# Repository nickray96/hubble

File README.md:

# hubble
A switched USB hub. 

# Rev 1.0:
* USB 2.0 and USB 3.0
* Tested working (see errata)
* Toggle SW1 to select between host 1 and 2
* Debug connector provides I2C to use via TotalPhase Aardvark (or other debug device)
  * Also routed to USB-C SBU

## Errata
* USB5744 does not enter runtime, looks for I2C host. Remove R14 and R17, puts hub in headless mode.

# Rev 2.0:
* Enable USB5744 port power toggling
* Optionally drive mux sel via Raspberry Pi Pico W (useful for home automation)
* Add DisplayPort mux so I can stop using my monitor OSD (TBD which connectors I'll use)

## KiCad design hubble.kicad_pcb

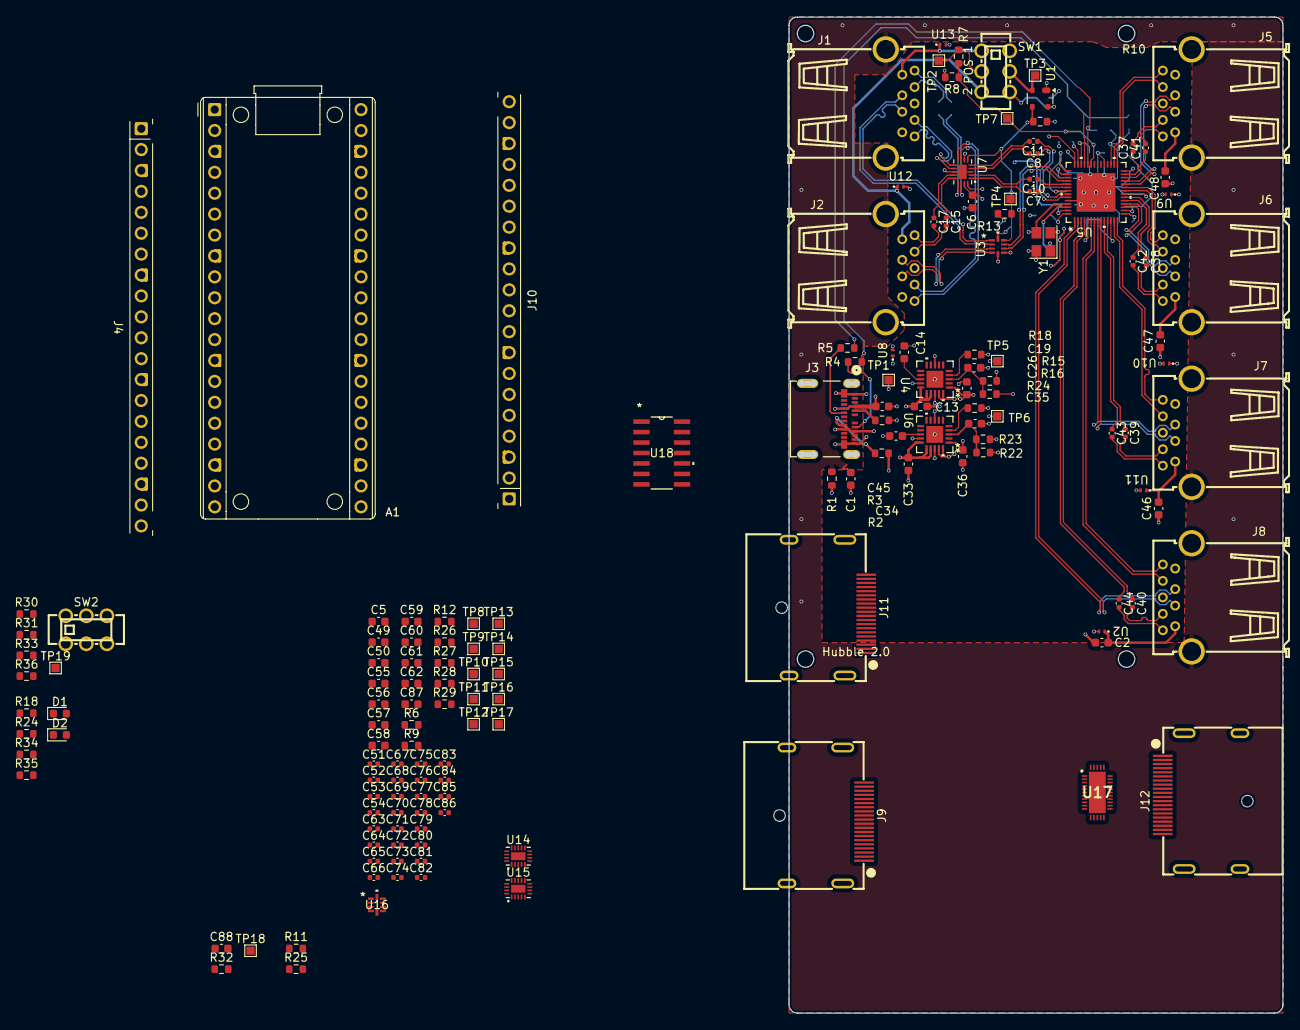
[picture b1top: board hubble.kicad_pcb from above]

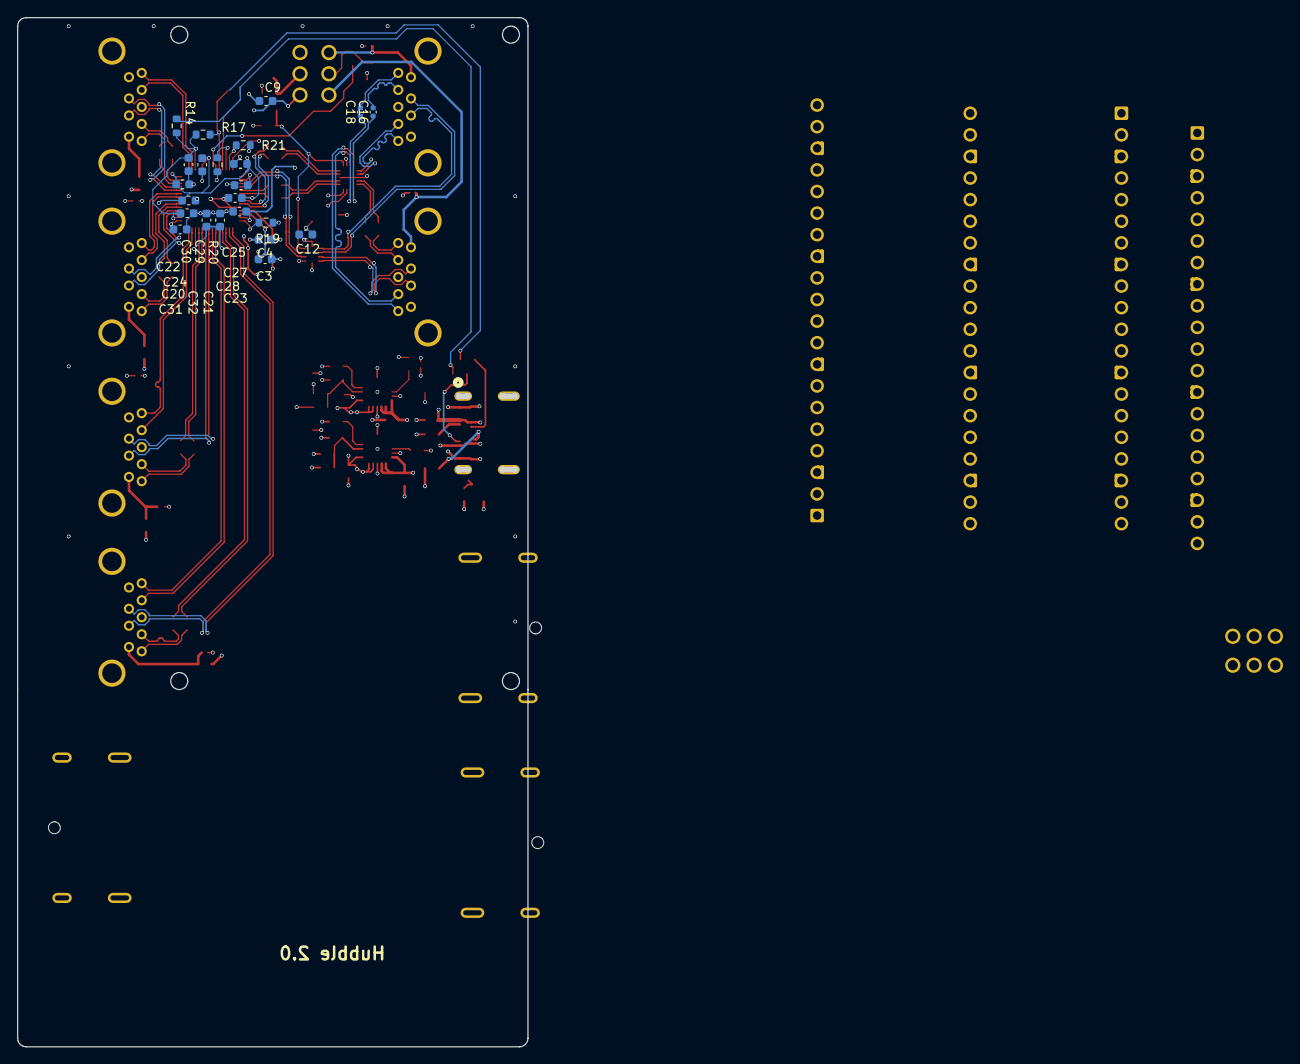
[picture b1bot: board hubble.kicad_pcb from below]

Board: 4 copper layers, 61.9 x 121.0 mm, 181 parts (23 on the bottom side), 181 nets.

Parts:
A1: RaspberryPi_Pico_W; RaspberryPi_Pico_Common_THT
C1, C5, C6, C9, C12, C14, C19, C20, C21, C22, C23, C24, C25, C27, C28, C29, C30, C31, C32, C34, C35, C49, C50, C55, C56, C57, C58, C59, C60, C61, C87, C88: 0.1uF; C_0603_1608Metric
C2, C45, C46, C47, C48: 2.2uF; C_0603_1608Metric
C3, C4: 20pF; C_0603_1608Metric
C7, C8, C10, C11, C15, C16, C17, C18, C37, C38, C39, C40, C41, C42, C43, C44, C51, C52, C53, C54, C63, C64, C65, C66, C67, C68, C69, C70, C71, C72, C73, C74, C75, C76, C77, C78, C79, C80, C81, C82, C83, C84, C85, C86: 0.1uF; C_0402_1005Metric
C13, C33: 10uF; C_0603_1608Metric
C26, C36: 22uF; C_0603_1608Metric
C62: 4.7uF; C_0603_1608Metric
D1, D2: LED_green; LED_0603_1608Metric
J1, J2, J5, J6, J7, J8: USB3_A_LCSC; USB-TH_XUNPU_USB-301WD-ARY
J3: USB_C_Receptacle_Molex; USB_C_CONN_105450-0101_MOLEX
J4: Pico_Socket_A; RaspberryPi_Pico_PinSocket_1x20_P2.54mm_Vertical
J9, J11, J12: DisplayPort; DISPLAYPORT_XDPF-0205-20S
J10: Pico_Socket_B; RaspberryPi_Pico_PinSocket_1x20_P2.54mm_Vertical
R1, R6, R9, R24#2, R29, R35: 330; R_0603_1608Metric
R2, R3: 5.1k; R_0603_1608Metric
R4, R5, R11, R25: 0; R_0603_1608Metric
R7, R18, R24: 50k; R_0603_1608Metric
R8: 100k; R_0603_1608Metric
R10, R13, R14, R17, R18#2, R26, R27, R30, R32, R34, R36: 10k; R_0603_1608Metric
R12, R28: 1M; R_0603_1608Metric
R15: 11.8k; R_0603_1608Metric
R16: 3.74k; R_0603_1608Metric
R19: 12k; R_0603_1608Metric
R20, R21: 200k; R_0603_1608Metric
R22: 12.4k; R_0603_1608Metric
R23: 24.9k; R_0603_1608Metric
R31, R33: 27; R_0603_1608Metric
SW1, SW2: K3-2235D-F1; SW-TH_K3-2235D-F1
TP1, TP2, TP3, TP4, TP5, TP6, TP7, TP8, TP9, TP10, TP11, TP12, TP13, TP14, TP15, TP16, TP17, TP18, TP19: TestPoint; TestPoint_Pad_1.0x1.0mm
U1: MAX6816EUS+T; SOT-143
U2, U8, U9, U10, U11, U12, U13: TPD1E05U06DPY; Texas_DPY0002A_0.6x1mm_P0.65mm
U3, U16: TS3USB221RSER; UQFN-10
U4, U6: TPS7A5201QRGRRQ1; RGR20_2P05X2P05_TEX
U5: USB5744; VQFN56_2G_MCH
U7, U14, U15: FUSB340; TMLP-18_L2.8-W2.0-P0.40-BL-EP
U17: PI3DPX1203BZLEX; QFN40P300X600X80-33N
U18: SN74CBTLV3126DR; D14
Y1: X322525MOB4SI; Crystal_SMD_3225-4Pin_3.2x2.5mm

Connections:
/DisplayPort/DP_HOST0_AUX_N: C54.2, U16.2 (1D-)
/DisplayPort/DP_HOST0_AUX_P: C51.2, U16.1 (1D+)
/DisplayPort/DP_HOST0_D0_N: C64.1, J9.3 (D0_N)
/DisplayPort/DP_HOST0_D0_P: C63.1, J9.1 (D0_P)
/DisplayPort/DP_HOST0_D1_N: C66.1, J9.6 (D1_N)
/DisplayPort/DP_HOST0_D1_P: C65.1, J9.4 (D1_P)
/DisplayPort/DP_HOST0_D2_N: C68.1, J9.9 (D2_N)
/DisplayPort/DP_HOST0_D2_P: C67.1, J9.7 (D2_P)
/DisplayPort/DP_HOST0_D3_N: C70.1, J9.12 (D3_N)
/DisplayPort/DP_HOST0_D3_P: C69.1, J9.10 (D3_P)
/DisplayPort/DP_HOST0_HPD: J9.18 (HPD), U18.2 (1A)
/DisplayPort/DP_HOST1_AUX_N: C53.2, U16.4 (2D-)
/DisplayPort/DP_HOST1_AUX_P: C52.2, U16.3 (2D+)
/DisplayPort/DP_HOST1_D0_N: C81.1, J11.3 (D0_N)
/DisplayPort/DP_HOST1_D0_P: C79.1, J11.1 (D0_P)
/DisplayPort/DP_HOST1_D1_N: C85.1, J11.6 (D1_N)
/DisplayPort/DP_HOST1_D1_P: C83.1, J11.4 (D1_P)
/DisplayPort/DP_HOST1_D2_N: C82.1, J11.9 (D2_N)
/DisplayPort/DP_HOST1_D2_P: C80.1, J11.7 (D2_P)
/DisplayPort/DP_HOST1_D3_N: C86.1, J11.12 (D3_N)
/DisplayPort/DP_HOST1_D3_P: C84.1, J11.10 (D3_P)
/DisplayPort/DP_HOST1_HPD: J11.18 (HPD), U18.5 (2A)
/DisplayPort/DP_SINK_AUX_N: J12.17 (AUX_N), U16.7 (D-)
/DisplayPort/DP_SINK_AUX_P: J12.15 (AUX_P), U16.8 (D+)
/DisplayPort/DP_SINK_HPD: J12.18 (HPD), U18.3 (1B), U18.6 (2B)
/DisplayPort/I2C_SCL: J4.5 (GPIO3), R5.2, R11.1, R14.2, U17.13 (SCL)
/DisplayPort/I2C_SDA: J4.4 (GPIO2), R4.2, R17.2, R25.1, U17.12 (SDA)
/DisplayPort/MUX_SEL: R10.1, R13.1, TP4.1, U1.3 (OUT), U3.9 (S), U7.6 (S), U14.6 (S), U15.6 (S), U16.9 (S), U18.4 (2OE)
/DisplayPort/~DP_RST: R27.1, U17.29 (FG1/I2C_RESET#)
/DisplayPort/~MUX_SEL: R32.1, TP18.1, U18.1 (1OE)
/Hub/DEVICE_1_USB_N: J8.2 (D-), U5.2 (USB2DN_DM1/PRT_DIS_M1)
/Hub/DEVICE_1_USB_P: J8.3 (D+), U5.1 (USB2DN_DP1/PRT_DIS_P1)
/Hub/DEVICE_2_USB_N: J7.2 (D-), U5.9 (USB2DN_DM2/PRT_DIS_M2)
/Hub/DEVICE_2_USB_P: J7.3 (D+), U5.8 (USB2DN_DP2/PRT_DIS_P2)
/Hub/DEVICE_3_USB_N: J6.2 (D-), U5.18 (USB2DN_DM3/PRT_DIS_M3)
/Hub/DEVICE_3_USB_P: J6.3 (D+), U5.17 (USB2DN_DP3/PRT_DIS_P3)
/Hub/DEVICE_4_USB_N: J5.2 (D-), U5.25 (USB2DN_DM4/PRT_DIS_M4)
/Hub/DEVICE_4_USB_P: J5.3 (D+), U5.24 (USB2DN_DP4/PRT_DIS_P4)
/Hub/HOST_1_USB_N: J1.2 (D-), U3.2 (1D-)
/Hub/HOST_1_USB_P: J1.3 (D+), U3.1 (1D+)
/Hub/HOST_2_USB_N: J2.2 (D-), U3.4 (2D-)
/Hub/HOST_2_USB_P: J2.3 (D+), U3.3 (2D+)
/Hub/HUB_USB_N: U3.7 (D-), U5.46 (USB2UP_DM)
/Hub/HUB_USB_P: U3.8 (D+), U5.45 (USB2UP_DP)
/Hub/SS_RX_DEVICE_1_N: J8.5 (SSRX-), U5.7 (USB3DN_RXDM1)
/Hub/SS_RX_DEVICE_1_P: J8.6 (SSRX+), U5.6 (USB3DN_RXDP1)
/Hub/SS_RX_DEVICE_2_N: J7.5 (SSRX-), U5.14 (USB3DN_RXDM2)
/Hub/SS_RX_DEVICE_2_P: J7.6 (SSRX+), U5.13 (USB3DN_RXDP2)
/Hub/SS_RX_DEVICE_3_N: J6.5 (SSRX-), U5.23 (USB3DN_RXDM3)
/Hub/SS_RX_DEVICE_3_P: J6.6 (SSRX+), U5.22 (USB3DN_RXDP3)
/Hub/SS_RX_DEVICE_4_N: J5.5 (SSRX-), U5.30 (USB3DN_RXDM4)
/Hub/SS_RX_DEVICE_4_P: J5.6 (SSRX+), U5.29 (USB3DN_RXDP4)
/Hub/SS_RX_HOST_1_N: J1.5 (SSRX-), U7.10 (SSRX1+)
/Hub/SS_RX_HOST_1_P: J1.6 (SSRX+), U7.11 (SSRX1-)
/Hub/SS_RX_HOST_2_N: J2.5 (SSRX-), U7.9 (SSRX2-)
/Hub/SS_RX_HOST_2_P: J2.6 (SSRX+), U7.8 (SSRX2+)
/Hub/SS_RX_HUB_CAP_N: C8.1, U7.4 (SSRXCOM-)
/Hub/SS_RX_HUB_CAP_P: C7.1, U7.5 (SSRXCOM+)
/Hub/SS_RX_HUB_N: C8.2, U5.51 (USB3UP_RXDM)
/Hub/SS_RX_HUB_P: C7.2, U5.50 (USB3UP_RXDP)
/Hub/SS_TX_DEVICE_1_CAP_N: C40.1, U5.4 (USB3DN_TXDM1)
/Hub/SS_TX_DEVICE_1_CAP_P: C44.1, U5.3 (USB3DN_TXDP1)
/Hub/SS_TX_DEVICE_1_N: C40.2, J8.8 (SSTX-)
/Hub/SS_TX_DEVICE_1_P: C44.2, J8.9 (SSTX+)
/Hub/SS_TX_DEVICE_2_CAP_N: C39.1, U5.11 (USB3DN_TXDM2)
/Hub/SS_TX_DEVICE_2_CAP_P: C43.1, U5.10 (USB3DN_TXDP2)
/Hub/SS_TX_DEVICE_2_N: C39.2, J7.8 (SSTX-)
/Hub/SS_TX_DEVICE_2_P: C43.2, J7.9 (SSTX+)
/Hub/SS_TX_DEVICE_3_CAP_N: C38.1, U5.20 (USB3DN_TXDM3)
/Hub/SS_TX_DEVICE_3_CAP_P: C42.1, U5.19 (USB3DN_TXDP3)
/Hub/SS_TX_DEVICE_3_N: C38.2, J6.8 (SSTX-)
/Hub/SS_TX_DEVICE_3_P: C42.2, J6.9 (SSTX+)
/Hub/SS_TX_DEVICE_4_CAP_N: C37.1, U5.27 (USB3DN_TXDM4)
/Hub/SS_TX_DEVICE_4_CAP_P: C41.1, U5.26 (USB3DN_TXDP4)
/Hub/SS_TX_DEVICE_4_N: C37.2, J5.8 (SSTX-)
/Hub/SS_TX_DEVICE_4_P: C41.2, J5.9 (SSTX+)
/Hub/SS_TX_HOST_1_CAP_N: C16.2, U7.15 (SSTX1+)
/Hub/SS_TX_HOST_1_CAP_P: C15.2, U7.16 (SSTX1-)
/Hub/SS_TX_HOST_1_N: C16.1, J1.8 (SSTX-)
/Hub/SS_TX_HOST_1_P: C15.1, J1.9 (SSTX+)
/Hub/SS_TX_HOST_2_CAP_N: C17.2, U7.14 (SSTX2-)
/Hub/SS_TX_HOST_2_CAP_P: C18.2, U7.13 (SSTX2+)
/Hub/SS_TX_HOST_2_N: C17.1, J2.8 (SSTX-)
/Hub/SS_TX_HOST_2_P: C18.1, J2.9 (SSTX+)
/Hub/SS_TX_HUB_CAP_N: C11.1, U7.1 (SSTXCOM-)
/Hub/SS_TX_HUB_CAP_P: C10.1, U7.2 (SSTXCOM+)
/Hub/SS_TX_HUB_N: C11.2, U5.48 (USB3UP_TXDM)
/Hub/SS_TX_HUB_P: C10.2, U5.47 (USB3UP_TXDP)
/Hub/VBUS_DET: R7.2, R8.1, TP7.1, U5.37 (VBUS_DET)
/Hub/VBUS_DET_1: J1.1 (VBUS), SW1.4 (A), U13.1 (I/O)
/Hub/VBUS_DET_2: J2.1 (VBUS), SW1.6 (C), U12.1 (I/O)
/MCU/MUX_SEL_MANUAL: SW1.2 (B), SW2.1 (A)
/MCU/MUX_SEL_MCU: J4.1 (GPIO0), R30.1, SW2.3 (C)
/MCU/PI_RUN: J10.10 (RUN), SW2.5 (B)
/Power/MCU_USB_DN: J3.A7 (D-), J3.B7 (D-)
/Power/MCU_USB_DP: J3.A6 (D+), J3.B6 (D+)
GND: C1.1, C2.1, C3.1, C4.1, C5.1, C6.1, C9.1, C12.1, C13.1, C14.1, C20.2, C21.2, C22.2, C23.2, C24.2, C25.2, C26.1, C27.2, C28.2, C29.2, C30.2, C31.2, C32.2, C33.1, C34.1, C36.1, C45.1, C46.1, C47.1, C48.1, C49.1, C50.1, C55.1, C56.1, C57.1, C58.2, C59.2, C60.2, C61.2, C62.2, C87.1, C88.1, J1.4 (GND), J1.7 (DRAIN), J2.4 (GND), J2.7 (DRAIN), J3.A1 (GND), J3.A12 (GND), J3.B1 (GND), J3.B12 (GND), J4.3 (GND), J4.8 (GND), J4.13 (GND), J4.18 (GND), J5.4 (GND), J5.7 (DRAIN), J6.4 (GND), J6.7 (DRAIN), J7.4 (GND), J7.7 (DRAIN), J8.4 (GND), J8.7 (DRAIN), J9.2 (GND), J9.5 (GND), J9.8 (GND), J9.11 (GND), J9.16 (GND), J10.3 (GND), J10.8 (GND), J10.13 (AGND), J10.18 (GND), J11.2 (GND), J11.5 (GND), J11.8 (GND), J11.11 (GND), J11.16 (GND), J12.19 (DP_PWR_RET), R1.2, R2.2, R3.2, R6.2, R8.2, R9.2, R10.2, R12.2, R13.2, R16.2, R19.1, R20.2, R21.2, R23.2, R24#2.2, R27.2, R28.2, R29.2, R30.2, R32.2, R35.2, SW1.1 (A), SW2.4 (A), U1.1 (GND), U2.2 (GND), U3.5 (GND), U3.6 (*OE), U4.8 (GND), U4.18 (GND), U4.21 (EPAD), U5.52 (ATEST), U5.57 (PAD), U6.8 (GND), U6.18 (GND), U6.21 (EPAD), U7.3 (GND), U7.7 (OE#), U7.12 (GND), U7.18 (GND), U7.19 (GND), U8.2 (GND), U9.2 (GND), U10.2 (GND), U11.2 (GND), U12.2 (GND), U13.2 (GND), U14.3 (GND), U14.7 (OE#), U14.12 (GND), U14.18 (GND), U14.19 (GND), U15.3 (GND), U15.7 (OE#), U15.12 (GND), U15.18 (GND), U15.19 (GND), U16.5 (GND), U16.6 (*OE), U17.14 (PRSNT#), U17.33 (GND), U18.7 (GND), Y1.2, Y1.4
unnamed: A1.3 (GND), A1.8 (GND), A1.13 (GND), A1.18 (GND), A1.23 (GND), A1.28 (GND), A1.38 (GND)
unnamed: D1.2 (A), R34.2, U6.4 (PG)
unnamed: D1.1 (K), R24#2.1
unnamed: D2.2 (A), R18#2.2, U4.4 (PG)
unnamed: D2.1 (K), R35.1
unnamed: J3.A5 (CC1), R3.1
unnamed: J3.B5 (CC2), R2.1
unnamed: J3.A8 (SBU1), R4.1
unnamed: J3.B8 (SBU2), R5.1
unnamed: C54.1, J9.17 (AUX_N)
unnamed: C51.1, J9.15 (AUX_P)
unnamed: J9.13 (CFG1), TP13.1
unnamed: J9.14 (CFG2), TP14.1
unnamed: C53.1, J11.17 (AUX_N)
unnamed: C52.1, J11.15 (AUX_P)
unnamed: J11.13 (CFG1), TP11.1
unnamed: J11.14 (CFG2), TP12.1
unnamed: J12.13 (CFG1), R28.1
unnamed: J12.14 (CFG2), R12.1
unnamed: C73.2, J12.3 (D0_N)
unnamed: C71.2, J12.1 (D0_P)
unnamed: C77.2, J12.6 (D1_N)
unnamed: C75.2, J12.4 (D1_P)
unnamed: C74.2, J12.9 (D2_N)
unnamed: C72.2, J12.7 (D2_P)
unnamed: C78.2, J12.12 (D3_N)
unnamed: C76.2, J12.10 (D3_P)
unnamed: R7.1, SW1.5 (B), TP2.1
unnamed: R36.2, SW2.6 (C)
unnamed: SW2.2 (B), TP3.1, U1.2 (IN)
unnamed: C19.1, R15.2, R16.1, U4.3 (FB)
unnamed: C14.2, U4.13 (NR/SS)
unnamed: R19.2, U5.56 (RBIAS)
unnamed: R21.1, U5.41 (SPI_CE_N/CFG_NON_REM)
unnamed: R11.2, U5.38 (SPI_CLK/SMCLK)
unnamed: R20.1, U5.40 (SPI_DI/CFG_BC_EN)
unnamed: R25.2, U5.39 (SPI_DO/SMDAT)
unnamed: C3.2, U5.54 (XTALI/CLK_IN), Y1.1
unnamed: C4.2, U5.53 (XTALO), Y1.3
unnamed: C35.1, R22.2, R23.1, U6.3 (FB)
unnamed: C34.2, U6.13 (NR/SS)
unnamed: C65.2, U14.10 (SSRX1+)
unnamed: C66.2, U14.11 (SSRX1-)
unnamed: C83.2, U14.8 (SSRX2+)
unnamed: C85.2, U14.9 (SSRX2-)
unnamed: U14.5 (SSRXCOM+), U17.4 (A1RX+)
unnamed: U14.4 (SSRXCOM-), U17.5 (A1RX-)
unnamed: C63.2, U14.15 (SSTX1+)
unnamed: C64.2, U14.16 (SSTX1-)
unnamed: C79.2, U14.13 (SSTX2+)
unnamed: C81.2, U14.14 (SSTX2-)
unnamed: U14.2 (SSTXCOM+), U17.1 (A0RX+)
unnamed: U14.1 (SSTXCOM-), U17.2 (A0RX-)
unnamed: C69.2, U15.10 (SSRX1+)
unnamed: C70.2, U15.11 (SSRX1-)
unnamed: C84.2, U15.8 (SSRX2+)
unnamed: C86.2, U15.9 (SSRX2-)
unnamed: U15.5 (SSRXCOM+), U17.10 (A3RX+)
unnamed: U15.4 (SSRXCOM-), U17.11 (A3RX-)
unnamed: C67.2, U15.15 (SSTX1+)
unnamed: C68.2, U15.16 (SSTX1-)
unnamed: C80.2, U15.13 (SSTX2+)
unnamed: C82.2, U15.14 (SSTX2-)
unnamed: U15.2 (SSTXCOM+), U17.7 (A2RX+)
unnamed: U15.1 (SSTXCOM-), U17.8 (A2RX-)
unnamed: C73.1, U17.27 (A0TX+)
unnamed: C71.1, U17.26 (A0TX-)
unnamed: C77.1, U17.24 (A1TX+)
unnamed: C75.1, U17.23 (A1TX-)
unnamed: C74.1, U17.21 (A2TX+)
unnamed: C72.1, U17.20 (A2TX-)
unnamed: C78.1, U17.18 (A3TX+)
unnamed: C76.1, U17.17 (A3TX-)
unnamed: R26.2, U17.15 (ENI2C)
unnamed: TP16.1, U18.9 (3A)
unnamed: TP17.1, U18.8 (3B)
unnamed: TP15.1, U18.10 (3OE)
unnamed: TP9.1, U18.12 (4A)
unnamed: TP10.1, U18.11 (4B)
unnamed: TP8.1, U18.13 (4OE)
Shield: C1.2, C5.2, C49.2, C55.2, J1.10 (SHIELD), J2.10 (SHIELD), J5.10 (SHIELD), J6.10 (SHIELD), J7.10 (SHIELD), J8.10 (SHIELD), J12.2 (GND), J12.5 (GND), J12.8 (GND), J12.11 (GND), J12.16 (GND), R1.1, R6.1, R9.1, R29.1
VBUS_IN: C2.2, C13.2, C33.2, C45.2, C46.2, C47.2, C48.2, J3.A4 (VBUS), J3.A9 (VBUS), J3.B4 (VBUS), J3.B9 (VBUS), J5.1 (VBUS), J6.1 (VBUS), J7.1 (VBUS), J8.1 (VBUS), J10.19 (VSYS), J10.20 (VBUS), TP1.1, U2.1 (I/O), U4.14 (EN), U4.15 (IN), U4.16 (IN), U4.17 (IN), U6.14 (EN), U6.15 (IN), U6.16 (IN), U6.17 (IN), U8.1 (I/O), U9.1 (I/O), U10.1 (I/O), U11.1 (I/O)
VCC_1.2V: C21.1, C22.1, C24.1, C25.1, C28.1, C29.1, C31.1, C32.1, C35.2, C36.2, R22.1, R24.1, TP6.1, U5.5 (VDD12), U5.12 (VDD12), U5.15 (VDD12), U5.21 (VDD12), U5.28 (VDD12), U5.33 (VDD12), U5.43 (VDD12), U5.49 (VDD12), U6.1 (OUT), U6.19 (OUT), U6.20 (OUT)
VCC_3.3V: C6.2, C9.2, C12.2, C19.2, C20.1, C23.1, C26.2, C27.1, C30.1, C50.2, C56.2, C57.2, C58.1, C59.1, C60.1, C61.1, C62.1, C87.2, C88.2, J12.20 (DP_PWR), R14.1, R15.1, R17.1, R18.1, R18#2.1, R26.1, R34.1, R36.1, SW1.3 (C), TP5.1, U1.4 (VCC), U3.10 (VCC), U4.1 (OUT), U4.19 (OUT), U4.20 (OUT), U5.16 (VDD33), U5.31 (VDD33), U5.42 (RESET_N), U5.44 (VDD33), U5.55 (VDD33), U7.17 (VDD), U14.17 (VDD), U15.17 (VDD), U16.10 (VCC), U17.3 (VDD), U17.6 (VDD_2), U17.9 (VDD_3), U17.19 (VDD_4), U17.22 (VDD_5), U17.25 (VDD_6), U17.28 (FG0), U17.30 (EQ1/AD1), U17.31 (EQ2/AD2), U17.32 (EQ3/AD3), U18.14 (VCC)

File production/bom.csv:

Designator,Footprint,Quantity,Value,LCSC Part #
"C1, C10, C11, C12, C14, C15, C16, C17, C18, C19, C20, C21, C22, C23, C24, C25, C27, C28, C29, C30, C31, C32, C34, C35, C37, C38, C39, C40, C41, C42, C43, C44, C6, C7, C8, C9",0603,36,0.1uF,
"C13, C33",0603,2,10uF,
"C2, C45, C46, C47, C48",0603,5,2.2uF,
"C26, C36",0603,2,22uF,
"C3, C4",0603,2,20pF,
"J1, J2, J5, J6, J7, J8",USB-TH_XUNPU_USB-301WD-ARY,6,USB3_A_LCSC,C2895025
J3,USB_C_CONN_105450-0101_MOLEX,1,USB_C_Receptacle_Molex,C134092
J9,PinHeader_2x02_P2.54mm_Vertical,1,Conn_02x02_Odd_Even,
R1,0603,1,330,
"R10, R13, R14, R17",0603,4,10k,
R15,0603,1,11.8k,
R16,0603,1,3.74k,
"R18, R24, R7",0603,3,50k,
R19,0603,1,12k,
"R2, R3",0603,2,5.1k,
"R20, R21",0603,2,200k,
R22,0603,1,12.4k,
R23,0603,1,24.9k,
"R4, R5",0603,2,0,
R8,0603,1,100k,
SW1,SW-TH_K3-2235D-F1,1,K3-2235D-F1,C189615
"TP1, TP2, TP3, TP4, TP5, TP6, TP7",TestPoint_Pad_1.0x1.0mm,7,TestPoint,
U1,SOT-143,1,MAX6816EUS+T,C41637
"U10, U11, U12, U13, U2, U8, U9",Texas_DPY0002A_0.6x1mm_P0.65mm,7,TPD1E05U06DPY,C2937017
U3,UQFN-10,1,TS3USB221RSER,C130085
"U4, U6",RGR20_2P05X2P05_TEX,2,TPS7A5201QRGRRQ1,C523802
U5,VQFN56_2G_MCH,1,USB5744,C633621
U7,TMLP-18_L2.8-W2.0-P0.40-BL-EP,1,FUSB340,
Y1,Crystal_SMD_3225-4Pin_3.2x2.5mm,1,X322525MOB4SI,C9006

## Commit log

2025-01-13 Add Rev 1.0 files
2025-01-22 Works. Update README.md, add errata section
2025-02-25 Add ki-lime-pi-to-go submodule, upgrade to KiCad 9, put a Pico W and through hole header on the schematic
2025-02-25 Update README.md with Rev 2.0 goals
2025-03-31 Add 2:1 displayport mux using TS3DV642
2025-08-09 Use 2x FUSB340 mux for DisplayPort, break up schematic into hierarchical pages
2025-08-09 Add PI3DPX1203BZLEX DisplayPort redriver and start adding it to schematic
2025-08-09 Change all high-speed decoupling caps to 0402s
2025-08-10 Wiring up DisplayPort HPD signals
2025-08-10 Start wiring up Pi Pico
2025-08-10 Wire up more of the Pico
